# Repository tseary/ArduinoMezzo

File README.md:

# ArduinoMezzo
Arduino Mezzo is a functional half-scale replica of the Arduino Uno.<p/> 
<p/>

I created this project as a novelty and as an exercise in miniaturization. As much as possible, the components
are 50% of the size of the components on the real Uno. The pin headers are all 50 mil pitch instead of 100 mil, and
the LEDs are 0402's instead of 0805's. Some parts differ because a half-scale version doesn't exist - the
USB connector is a mini-B instead of B type, and the power jack is has a 2.5 mm OD instead of the standard 5.5 mm.<p/>

Functional differences include a simplified power supply, and a different chip entirely for the USB-serial bridge.
The real Uno power supply has comparators and MOSFETs to select between USB and battery power. The Mezzo simply
combines the two sources using schottky diodes. To program the Mezzo, you have to manually press the reset button
since there is no DTR reset as in the Uno.<p/>

I hope that this project amuses you as much as it did me. If you make your own Mezzo I'd love to see it!<p/>

Disclaimer: This is not an official Arduino product and I am not affiliated with Arduino in any way.
This design is made available for anyone to use for any purpose, at their own risk.

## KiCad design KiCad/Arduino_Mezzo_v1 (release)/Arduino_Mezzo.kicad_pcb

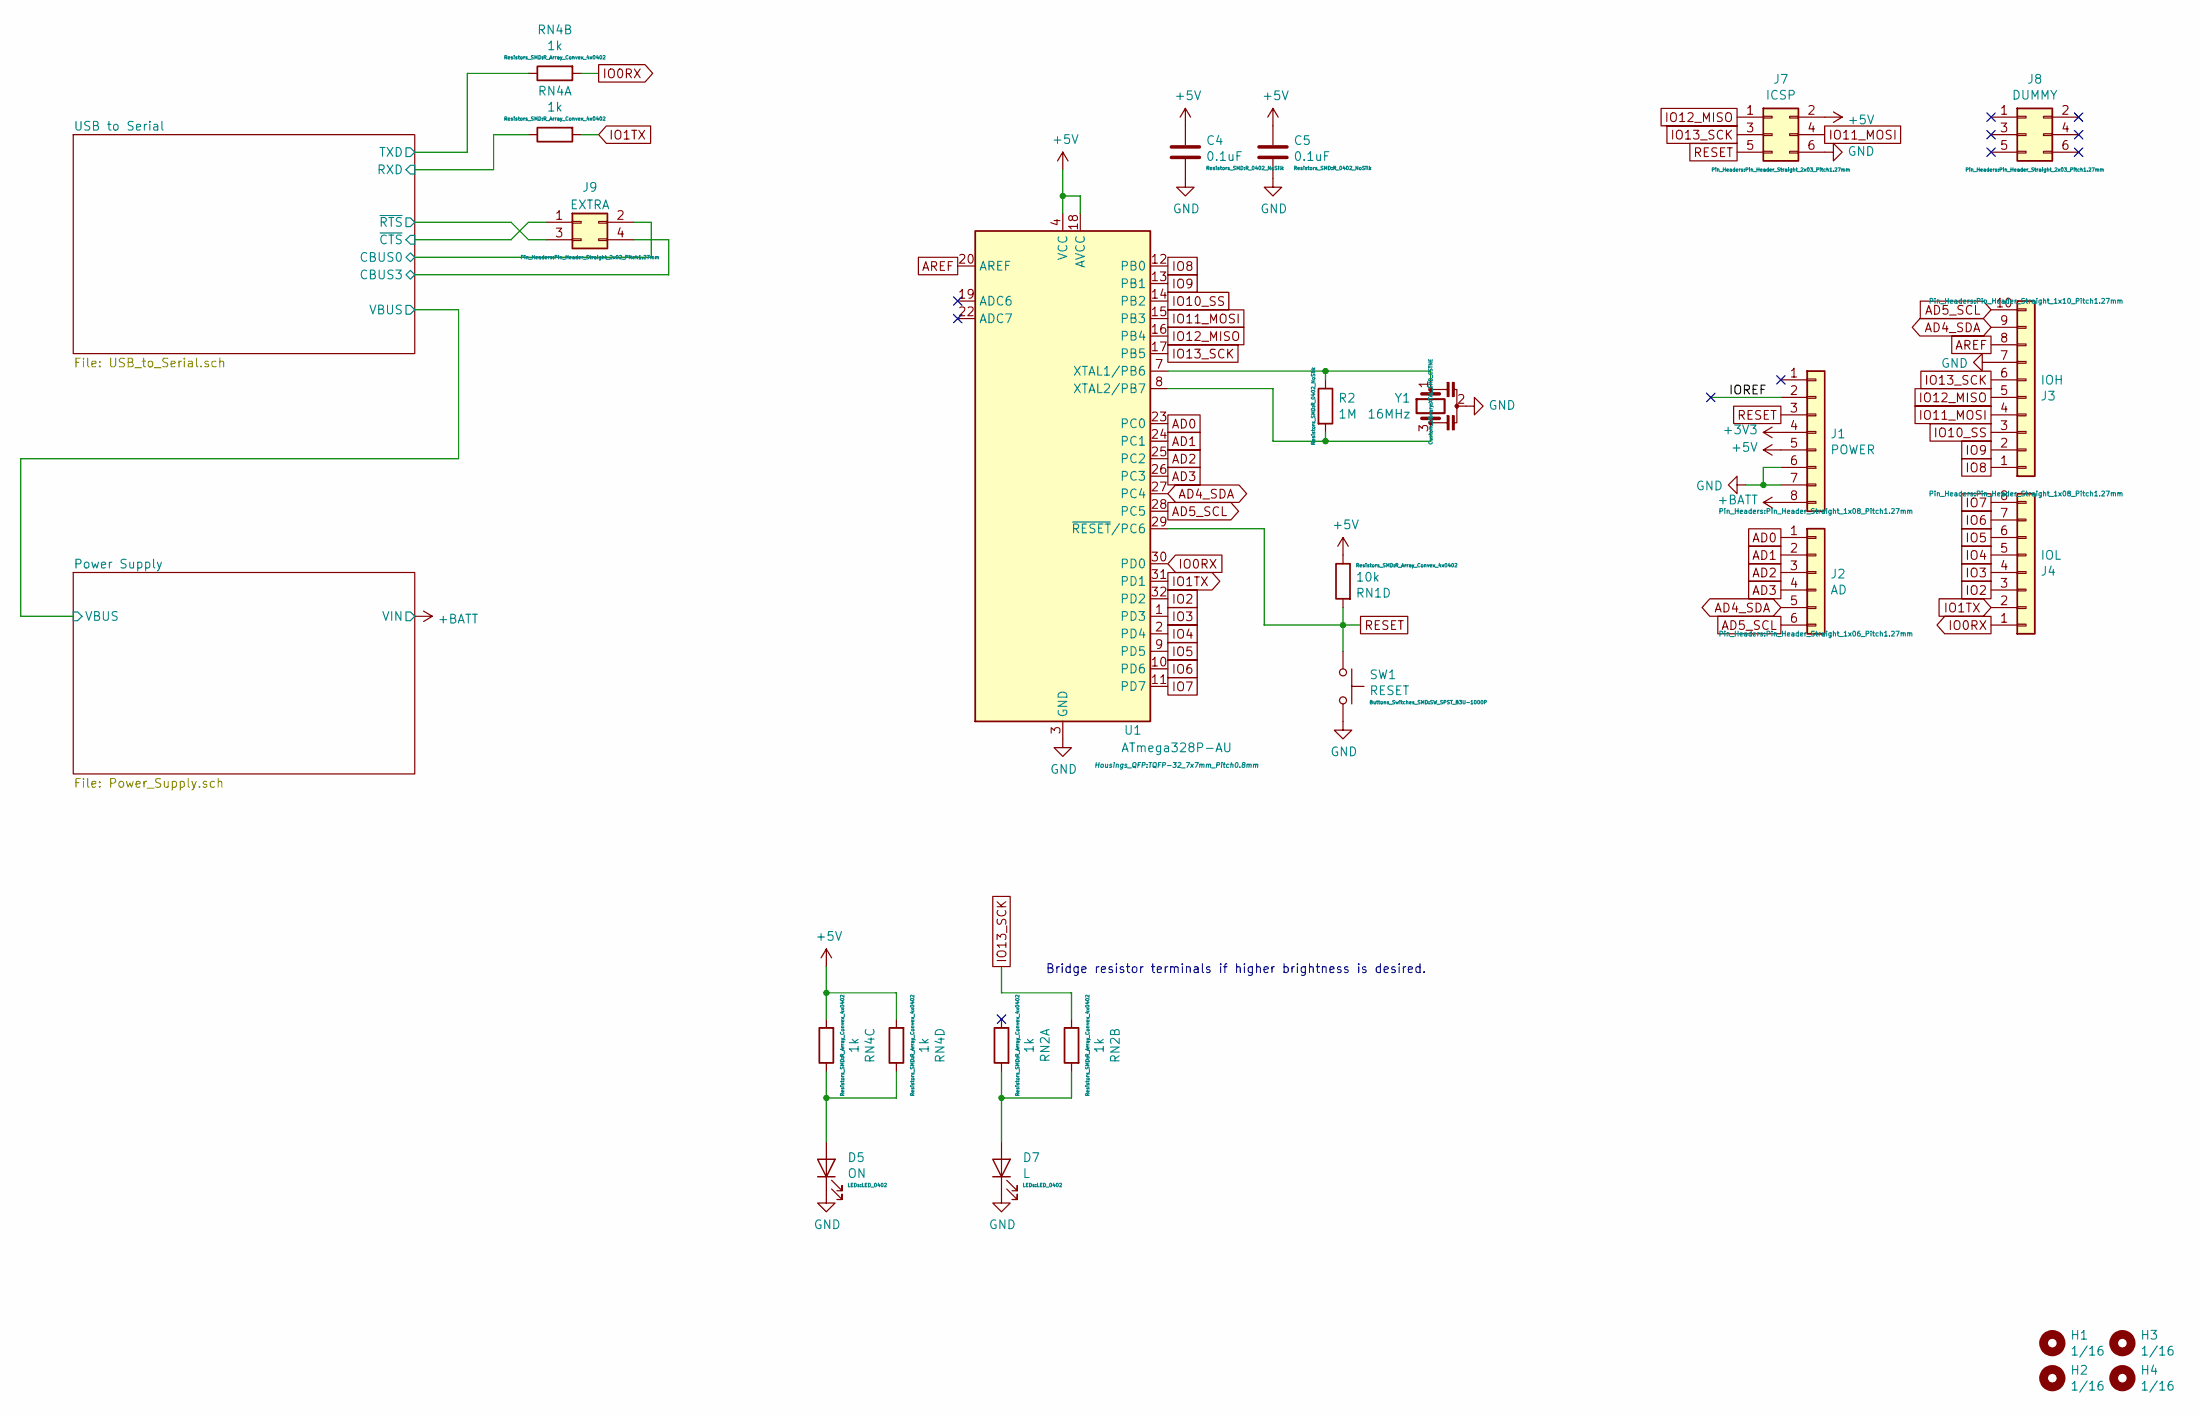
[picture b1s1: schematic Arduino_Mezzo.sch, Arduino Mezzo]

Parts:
C4, C5: 0.1uF; R_0402_NoSilk
D5: ON; LED_0402
D7: L; LED_0402
H1, H2, H3, H4: 1/16; M2_Isolated
J1: POWER; Pin_Header_Straight_1x08_Pitch1.27mm
J2: AD; Pin_Header_Straight_1x06_Pitch1.27mm
J3: IOH; Pin_Header_Straight_1x10_Pitch1.27mm
J4: IOL; Pin_Header_Straight_1x08_Pitch1.27mm
J7: ICSP; Pin_Header_Straight_2x03_Pitch1.27mm
J8: DUMMY; Pin_Header_Straight_2x03_Pitch1.27mm
J9: EXTRA; Pin_Header_Straight_2x02_Pitch1.27mm
R2: 1M; R_0402_NoSilk
RN1: 10k; R_Array_Convex_4x0402
RN2, RN4: 1k; R_Array_Convex_4x0402
SW1: RESET; SW_SPST_B3U-1000P
U1: ATmega328P-AU; TQFP-32_7x7mm_Pitch0.8mm
Y1: 16MHz; XTAL_SMD_CSTNE

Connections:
+3V3: J1.4; also elsewhere on the board
+5V: C4.1, C5.1, J1.5, J7.2, RN1.5, RN4.3, RN4.4, U1.4 (VCC), U1.6 (VCC), U1.18 (AVCC); also elsewhere on the board
+BATT: J1.8; also elsewhere on the board
/IOREF: J1.2
/USB to Serial/CBUS0: J9.2; also elsewhere on the board
/USB to Serial/CBUS3: J9.4; also elsewhere on the board
/USB to Serial/RXD: RN4.8; also elsewhere on the board
/USB to Serial/TXD: RN4.7; also elsewhere on the board
/USB to Serial/~CTS: J9.1; also elsewhere on the board
/USB to Serial/~RTS: J9.3; also elsewhere on the board
AD0: J2.1, U1.23 (PC0)
AD1: J2.2, U1.24 (PC1)
AD2: J2.3, U1.25 (PC2)
AD3: J2.4, U1.26 (PC3)
AD4_SDA: J2.5, J3.9, U1.27 (PC4)
AD5_SCL: J2.6, J3.10, U1.28 (PC5)
AREF: J3.8, U1.20 (AREF)
GND: C4.2, C5.2, D5.1 (K), D7.1 (K), J1.6, J1.7, J3.7, J7.6, SW1.2, U1.3 (GND), U1.5 (GND), U1.21 (GND), Y1.2; also elsewhere on the board
IO0RX: J4.1, RN4.2, U1.30 (PD0)
IO1TX: J4.2, RN4.1, U1.31 (PD1)
IO2: J4.3, U1.32 (PD2)
IO3: J4.4, U1.1 (PD3)
IO4: J4.5, U1.2 (PD4)
IO5: J4.6, U1.9 (PD5)
IO6: J4.7, U1.10 (PD6)
IO7: J4.8, U1.11 (PD7)
IO8: J3.1, U1.12 (PB0)
IO9: J3.2, U1.13 (PB1)
IO10_SS: J3.3, U1.14 (PB2)
IO11_MOSI: J3.4, J7.4, U1.15 (PB3)
IO12_MISO: J3.5, J7.1, U1.16 (PB4)
IO13_SCK: J3.6, J7.3, RN2.7, U1.17 (PB5)
unnamed: D5.2 (A), RN4.5, RN4.6
unnamed: D7.2 (A), RN2.1, RN2.2
unnamed: R2.1, U1.7 (XTAL1/PB6), Y1.1
unnamed: R2.2, U1.8 (XTAL2/PB7), Y1.3
RESET: J1.3, J7.5, RN1.4, SW1.1, U1.29 (~RESET~/PC6)

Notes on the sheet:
Bridge resistor terminals if higher brightness is desired.

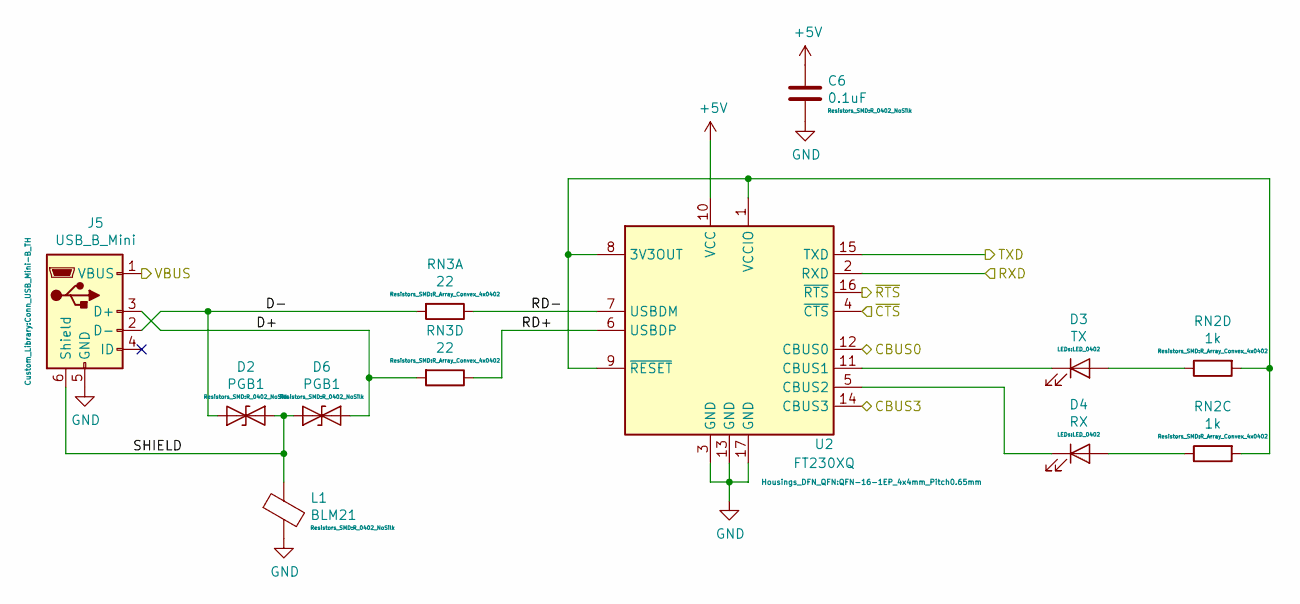
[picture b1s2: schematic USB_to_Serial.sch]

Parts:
C6: 0.1uF; R_0402_NoSilk
D2, D6: PGB1; R_0402_NoSilk
D3: TX; LED_0402
D4: RX; LED_0402
J5: USB_B_Mini; Conn_USB_Mini-B_TH
L1: BLM21; R_0402_NoSilk
RN2: 1k; R_Array_Convex_4x0402
RN3: 22; R_Array_Convex_4x0402
U2: FT230XQ; QFN-16-1EP_4x4mm_Pitch0.65mm

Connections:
+5V: C6.1, U2.10 (VCC); also elsewhere on the board
/Power Supply/VBUS: J5.1 (VBUS); also elsewhere on the board
/USB to Serial/CBUS0: U2.12 (CBUS0); also elsewhere on the board
/USB to Serial/CBUS3: U2.14 (CBUS3); also elsewhere on the board
/USB to Serial/D+: D6.2 (A2), J5.3 (D+), RN3.4
/USB to Serial/D-: D2.1 (A1), J5.2 (D-), RN3.1
/USB to Serial/RD+: RN3.5, U2.6 (USBDP)
/USB to Serial/RD-: RN3.8, U2.7 (USBDM)
/USB to Serial/RXD: U2.2 (RXD); also elsewhere on the board
/USB to Serial/SHIELD: D2.2 (A2), D6.1 (A1), J5.6 (Shield), L1.1
/USB to Serial/TXD: U2.15 (TXD); also elsewhere on the board
/USB to Serial/~CTS: U2.4 (~CTS); also elsewhere on the board
/USB to Serial/~RTS: U2.16 (~RTS); also elsewhere on the board
GND: C6.2, J5.5 (GND), L1.2, U2.3 (GND), U2.13 (GND), U2.17 (GND); also elsewhere on the board
unnamed: D3.1 (K), U2.11 (CBUS1)
unnamed: D3.2 (A), RN2.5
unnamed: D4.1 (K), U2.5 (CBUS2)
unnamed: D4.2 (A), RN2.6
unnamed: RN2.3, RN2.4, U2.1 (VCCIO), U2.8 (3V3OUT), U2.9 (~RESET)

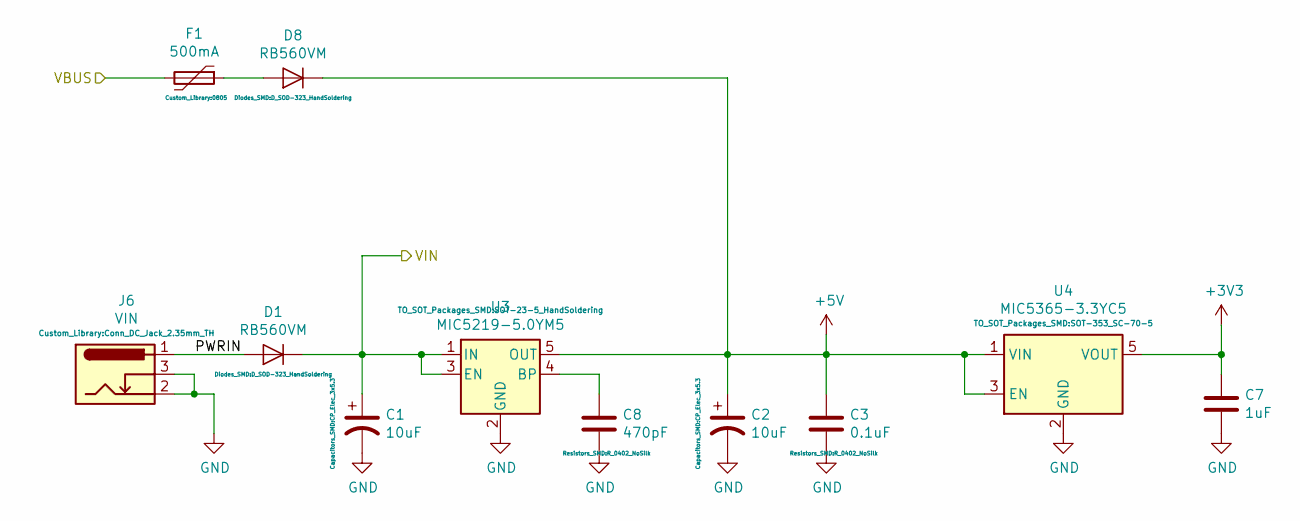
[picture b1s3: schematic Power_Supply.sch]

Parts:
C1, C2: 10uF; CP_Elec_3x5.3
C3: 0.1uF; R_0402_NoSilk
C7: 1uF; R_0402_NoSilk
C8: 470pF; R_0402_NoSilk
D1, D8: RB560VM; D_SOD-323_HandSoldering
F1: 500mA; 0805
J6: VIN; Conn_DC_Jack_2.35mm_TH
U3: MIC5219-5.0YM5; SOT-23-5_HandSoldering
U4: MIC5365-3.3YC5; SOT-353_SC-70-5

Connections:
+3V3: C7.1, U4.5 (VOUT); also elsewhere on the board
+5V: C2.1, C3.1, D8.1 (K), U3.5 (OUT), U4.1 (VIN), U4.3 (EN); also elsewhere on the board
+BATT: C1.1, D1.1 (K), U3.1 (IN), U3.3 (EN); also elsewhere on the board
/Power Supply/PWRIN: D1.2 (A), J6.1
/Power Supply/VBUS: F1.2; also elsewhere on the board
GND: C1.2, C2.2, C3.2, C7.2, C8.2, J6.2, J6.3, U3.2 (GND), U4.2 (GND); also elsewhere on the board
unnamed: C8.1, U3.4 (BP)
unnamed: D8.2 (A), F1.1

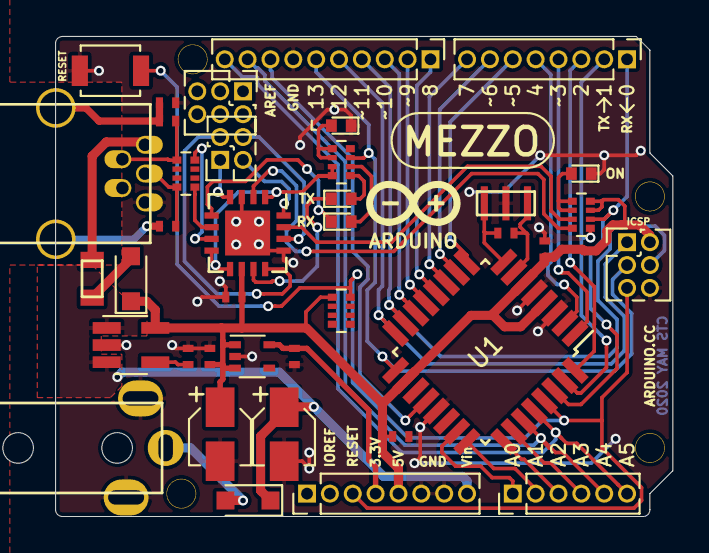
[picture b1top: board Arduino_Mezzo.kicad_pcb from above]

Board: 2 copper layers, 34.3 x 26.7 mm, 42 parts (0 on the bottom side), 50 nets.

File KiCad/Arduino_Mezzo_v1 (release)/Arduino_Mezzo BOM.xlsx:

Reference | Value | Footprint | Digikey Part # | In Cart | Datasheet
SW1 | RESET | Buttons_Switches_SMD:SW_SPST_B3U-1000P | SW1020CT-ND‎ | 3 | ~
C1 | 10uF | Capacitors_SMD:CP_Elec_3x5.3 | 338-1793-1-ND‎ | 6 | AVE106M16A12T-F
C2 | 10uF | Capacitors_SMD:CP_Elec_3x5.3 | 338-1793-1-ND‎ |  | AVE106M16A12T-F
F1 | 500mA | Custom_Library:0805 | 507-2075-1-ND‎ | 3 | 0ZCK0050AF2E
J6 | VIN | Custom_Library:Conn_DC_Jack_2.35mm_TH | 732-5920-ND‎ | 3 | ~
J5 | USB_B_Mini | Custom_Library:Conn_USB_Mini-B_TH | 54-00019T-ND‎ | 3 | 54-00019
H1 | 43846 | Custom_Library:M2_Isolated | N/A | 0 | ~
H2 | 43846 | Custom_Library:M2_Isolated | N/A |  | ~
H3 | 43846 | Custom_Library:M2_Isolated | N/A |  | ~
H4 | 43846 | Custom_Library:M2_Isolated | N/A |  | ~
Y1 | 16MHz | Custom_Library:XTAL_SMD_CSTNE | 490-17948-1-ND‎ | 3 | CSTNE16M0V530000R0
D1 | RB560VM | Diodes_SMD:D_SOD-323_HandSoldering | 1727-8169-1-ND‎ | 6 | ~
D8 | RB560VM | Diodes_SMD:D_SOD-323_HandSoldering | 1727-8169-1-ND‎ |  | ~
U2 | FT230XQ | Housings_DFN_QFN:QFN-16-1EP_4x4mm_Pitch0.65mm | 768-1130-1-ND‎ | 3 | https://www.ftdichip.com/Support/Documents/DataSheets/ICs/DS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
U1 | ATmega328P-AU | Housings_QFP:TQFP-32_7x7mm_Pitch0.8mm | ATMEGA328P-AU-ND | 3 | http://ww1.microchip.com/downloads/en/DeviceDoc/ATmega328_P%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
D5 | ON | LEDs:LED_0402 | 732-11992-1-ND‎ | 10 | ~
D7 | L | LEDs:LED_0402 | 732-11993-1-ND‎ | 10 | ~
D4 | RX | LEDs:LED_0402 | 732-11993-1-ND‎ |  | ~
D3 | TX | LEDs:LED_0402 | 732-11993-1-ND‎ |  | ~
J2 | AD | Pin_Headers:Pin_Header_Straight_1x06_Pitch1.27mm | S9008E-06-ND‎ | 3 | ~
J4 | IOL | Pin_Headers:Pin_Header_Straight_1x08_Pitch1.27mm | S9008E-08-ND‎ | 6 | ~
J1 | POWER | Pin_Headers:Pin_Header_Straight_1x08_Pitch1.27mm | S9008E-08-ND‎ |  | ~
J3 | IOH | Pin_Headers:Pin_Header_Straight_1x10_Pitch1.27mm | S9008E-10-ND‎ | 3 | ~
J9 | EXTRA | Pin_Headers:Pin_Header_Straight_2x02_Pitch1.27mm | N/A | 0 | ~
J8 | DUMMY | Pin_Headers:Pin_Header_Straight_2x03_Pitch1.27mm | S9015E-03-ND‎ | 6 | ~
J7 | ICSP | Pin_Headers:Pin_Header_Straight_2x03_Pitch1.27mm | S9015E-03-ND‎ |  | ~
C3 | 0.1uF | Resistors_SMD:R_0402_NoSilk | 732-7532-1-ND | 15 | ~
C4 | 0.1uF | Resistors_SMD:R_0402_NoSilk | 732-7532-1-ND |  | ~
C5 | 0.1uF | Resistors_SMD:R_0402_NoSilk | 732-7532-1-ND |  | ~
C6 | 0.1uF | Resistors_SMD:R_0402_NoSilk | 732-7532-1-ND |  | ~
R2 | 1M | Resistors_SMD:R_0402_NoSilk | RMCF0402FT1M00CT-ND | 10 | ~
C7 | 1uF | Resistors_SMD:R_0402_NoSilk | 399-4873-1-ND‎ | 10 | C0402C105K9PACTU
L1 | BLM21 | Resistors_SMD:R_0402_NoSilk | 445-2981-1-ND‎ | 3 | MPZ1005S121CT000
C8 | 470pF | Resistors_SMD:R_0402_NoSilk | 732-7554-1-ND‎ | 10 | ~
D2 | PGB1 | Resistors_SMD:R_0402_NoSilk | F2862CT-ND‎ | 6 | ~
D6 | PGB1 | Resistors_SMD:R_0402_NoSilk | F2862CT-ND‎ |  | ~
RN3 | 22 | Resistors_SMD:R_Array_Convex_4x0402 | 741X083220JPCT-ND | 3
RN1 | 10k | Resistors_SMD:R_Array_Convex_4x0402 | 741X083103JPCT-ND | 3
RN2 | 1k | Resistors_SMD:R_Array_Convex_4x0402 | 741X083102JPCT-ND | 6
RN4 | 1k | Resistors_SMD:R_Array_Convex_4x0402 | 741X083102JPCT-ND
U3 | MIC5219-5.0YM5 | TO_SOT_Packages_SMD:SOT-23-5_HandSoldering | 576-2770-1-ND‎ | 3 | http://ww1.microchip.com/downloads/en/DeviceDoc/MIC5219-500m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
U4 | MIC5365-3.3YC5 | TO_SOT_Packages_SMD:SOT-353_SC-70-5 | 576-3193-1-ND‎ | 3 | http://ww1.microchip.com/downloads/en/DeviceDoc/mic5365.pdf

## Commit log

2020-07-24 KiCad files
    Added the KiCad files used to create the first prototype.
